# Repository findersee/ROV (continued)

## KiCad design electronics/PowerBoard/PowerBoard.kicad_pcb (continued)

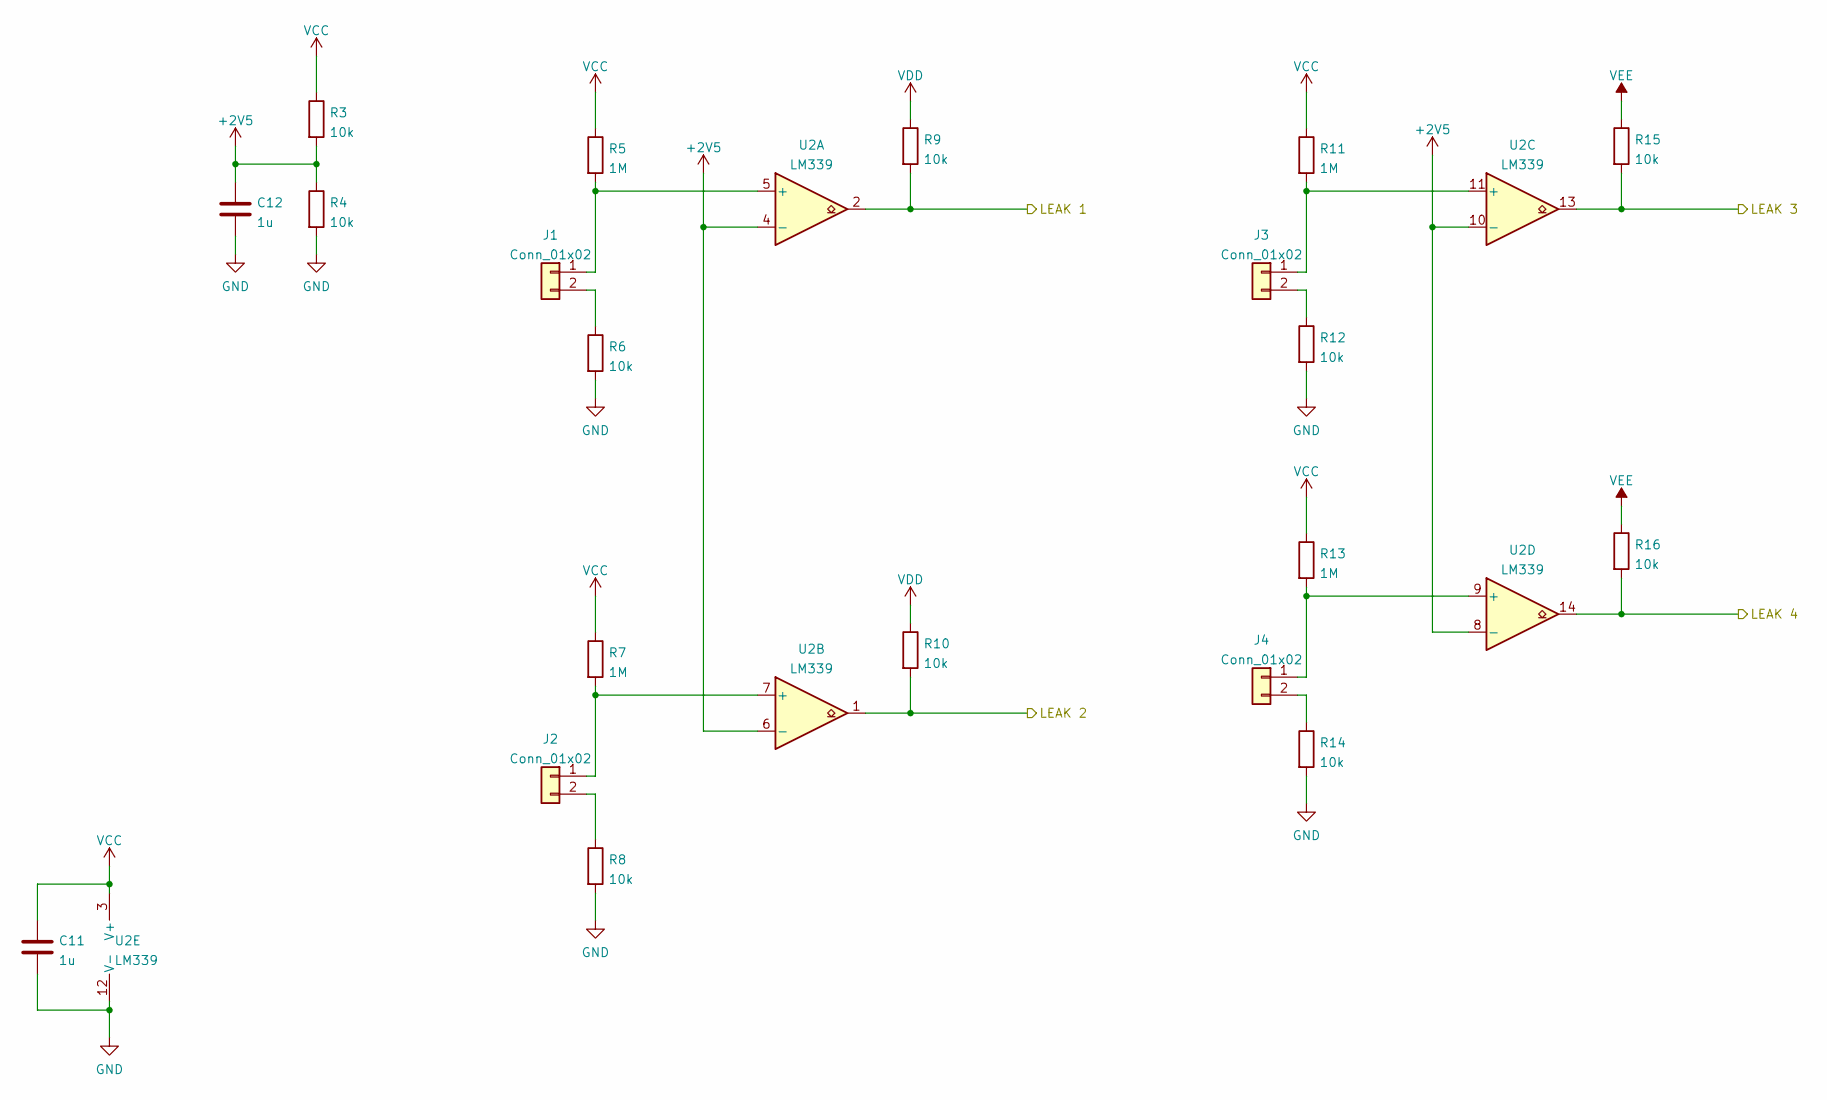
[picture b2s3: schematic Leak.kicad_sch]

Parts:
C11, C12: 1u; C_0805_2012Metric
J1, J2, J3, J4: Conn_01x02; PinHeader_1x02_P2.54mm_Vertical
R3, R4, R6, R8, R9, R10, R12, R14, R15, R16: 10k; R_0603_1608Metric
R5, R7, R11, R13: 1M; R_0603_1608Metric
U2: LM339; SOIC-14_3.9x8.7mm_P1.27mm

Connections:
+2V5: C12.1, R3.2, R4.1, U2.4 (-), U2.6 (-), U2.8 (-), U2.10 (-)
/Connectors/GP04: R10.2, U2.1; also elsewhere on the board
/Connectors/GP17: R9.2, U2.2; also elsewhere on the board
/Connectors/GP22: R15.2, U2.13; also elsewhere on the board
/Connectors/GP27: R16.2, U2.14; also elsewhere on the board
GND: C11.2, C12.2, R4.2, R6.2, R8.2, R12.2, R14.2, U2.12 (V-); also elsewhere on the board
unnamed: J1.1, R5.2, U2.5 (+)
unnamed: J1.2, R6.1
unnamed: J2.1, R7.2, U2.7 (+)
unnamed: J2.2, R8.1
unnamed: J3.1, R11.2, U2.11 (+)
unnamed: J3.2, R12.1
unnamed: J4.1, R13.2, U2.9 (+)
unnamed: J4.2, R14.1
VCC: C11.1, R3.1, R5.1, R7.1, R11.1, R13.1, U2.3 (V+); also elsewhere on the board
VDD: R9.1, R10.1; also elsewhere on the board
VEE: R15.1, R16.1; also elsewhere on the board

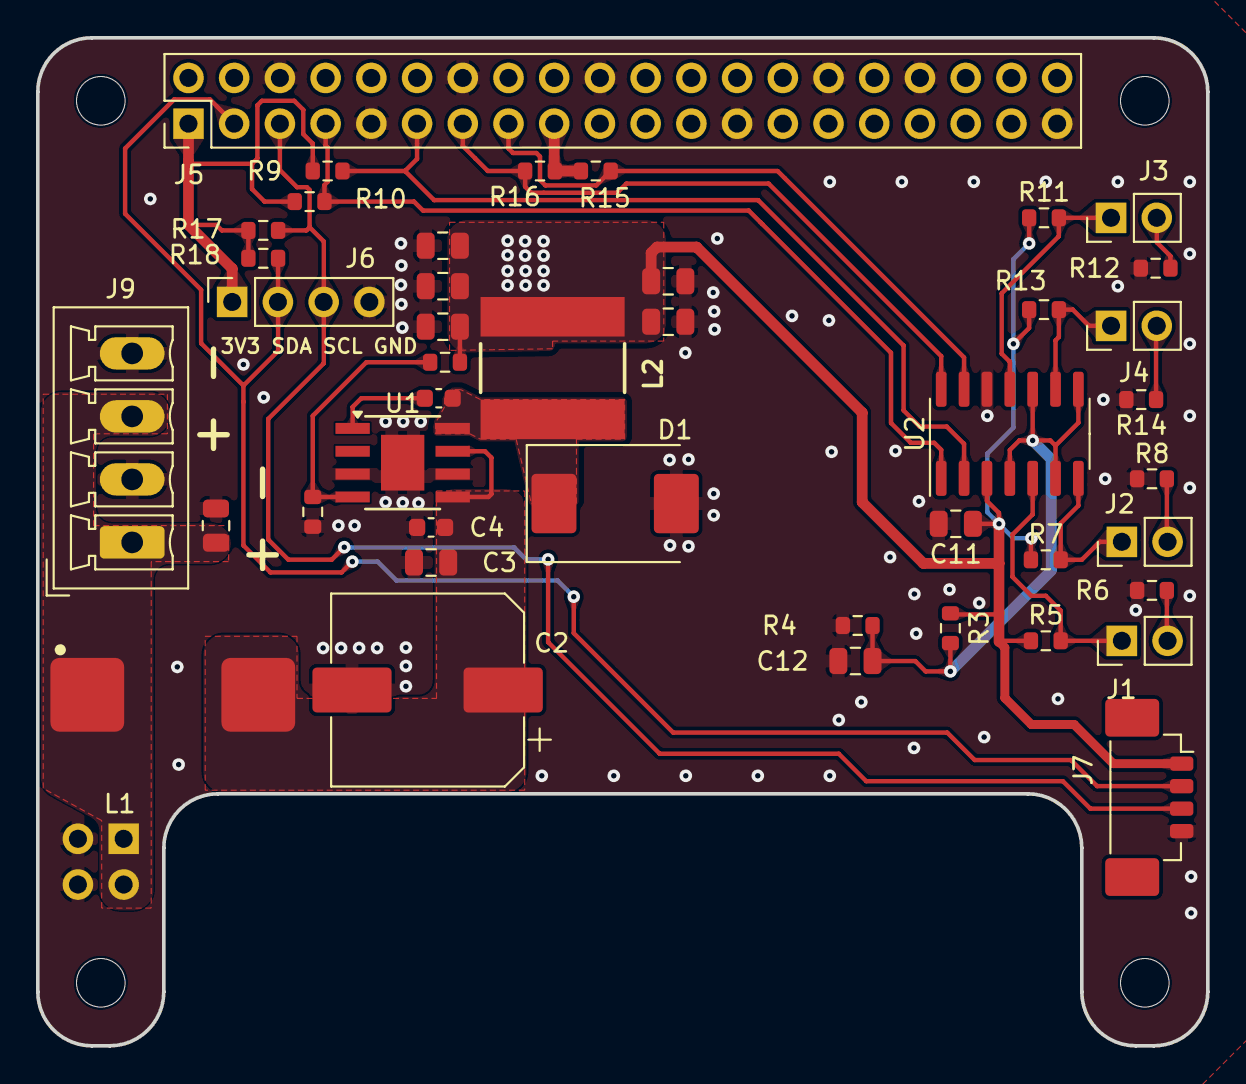
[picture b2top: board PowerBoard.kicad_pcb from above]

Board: 2 copper layers, 65.0 x 56.0 mm, 48 parts (1 on the bottom side), 24 nets.

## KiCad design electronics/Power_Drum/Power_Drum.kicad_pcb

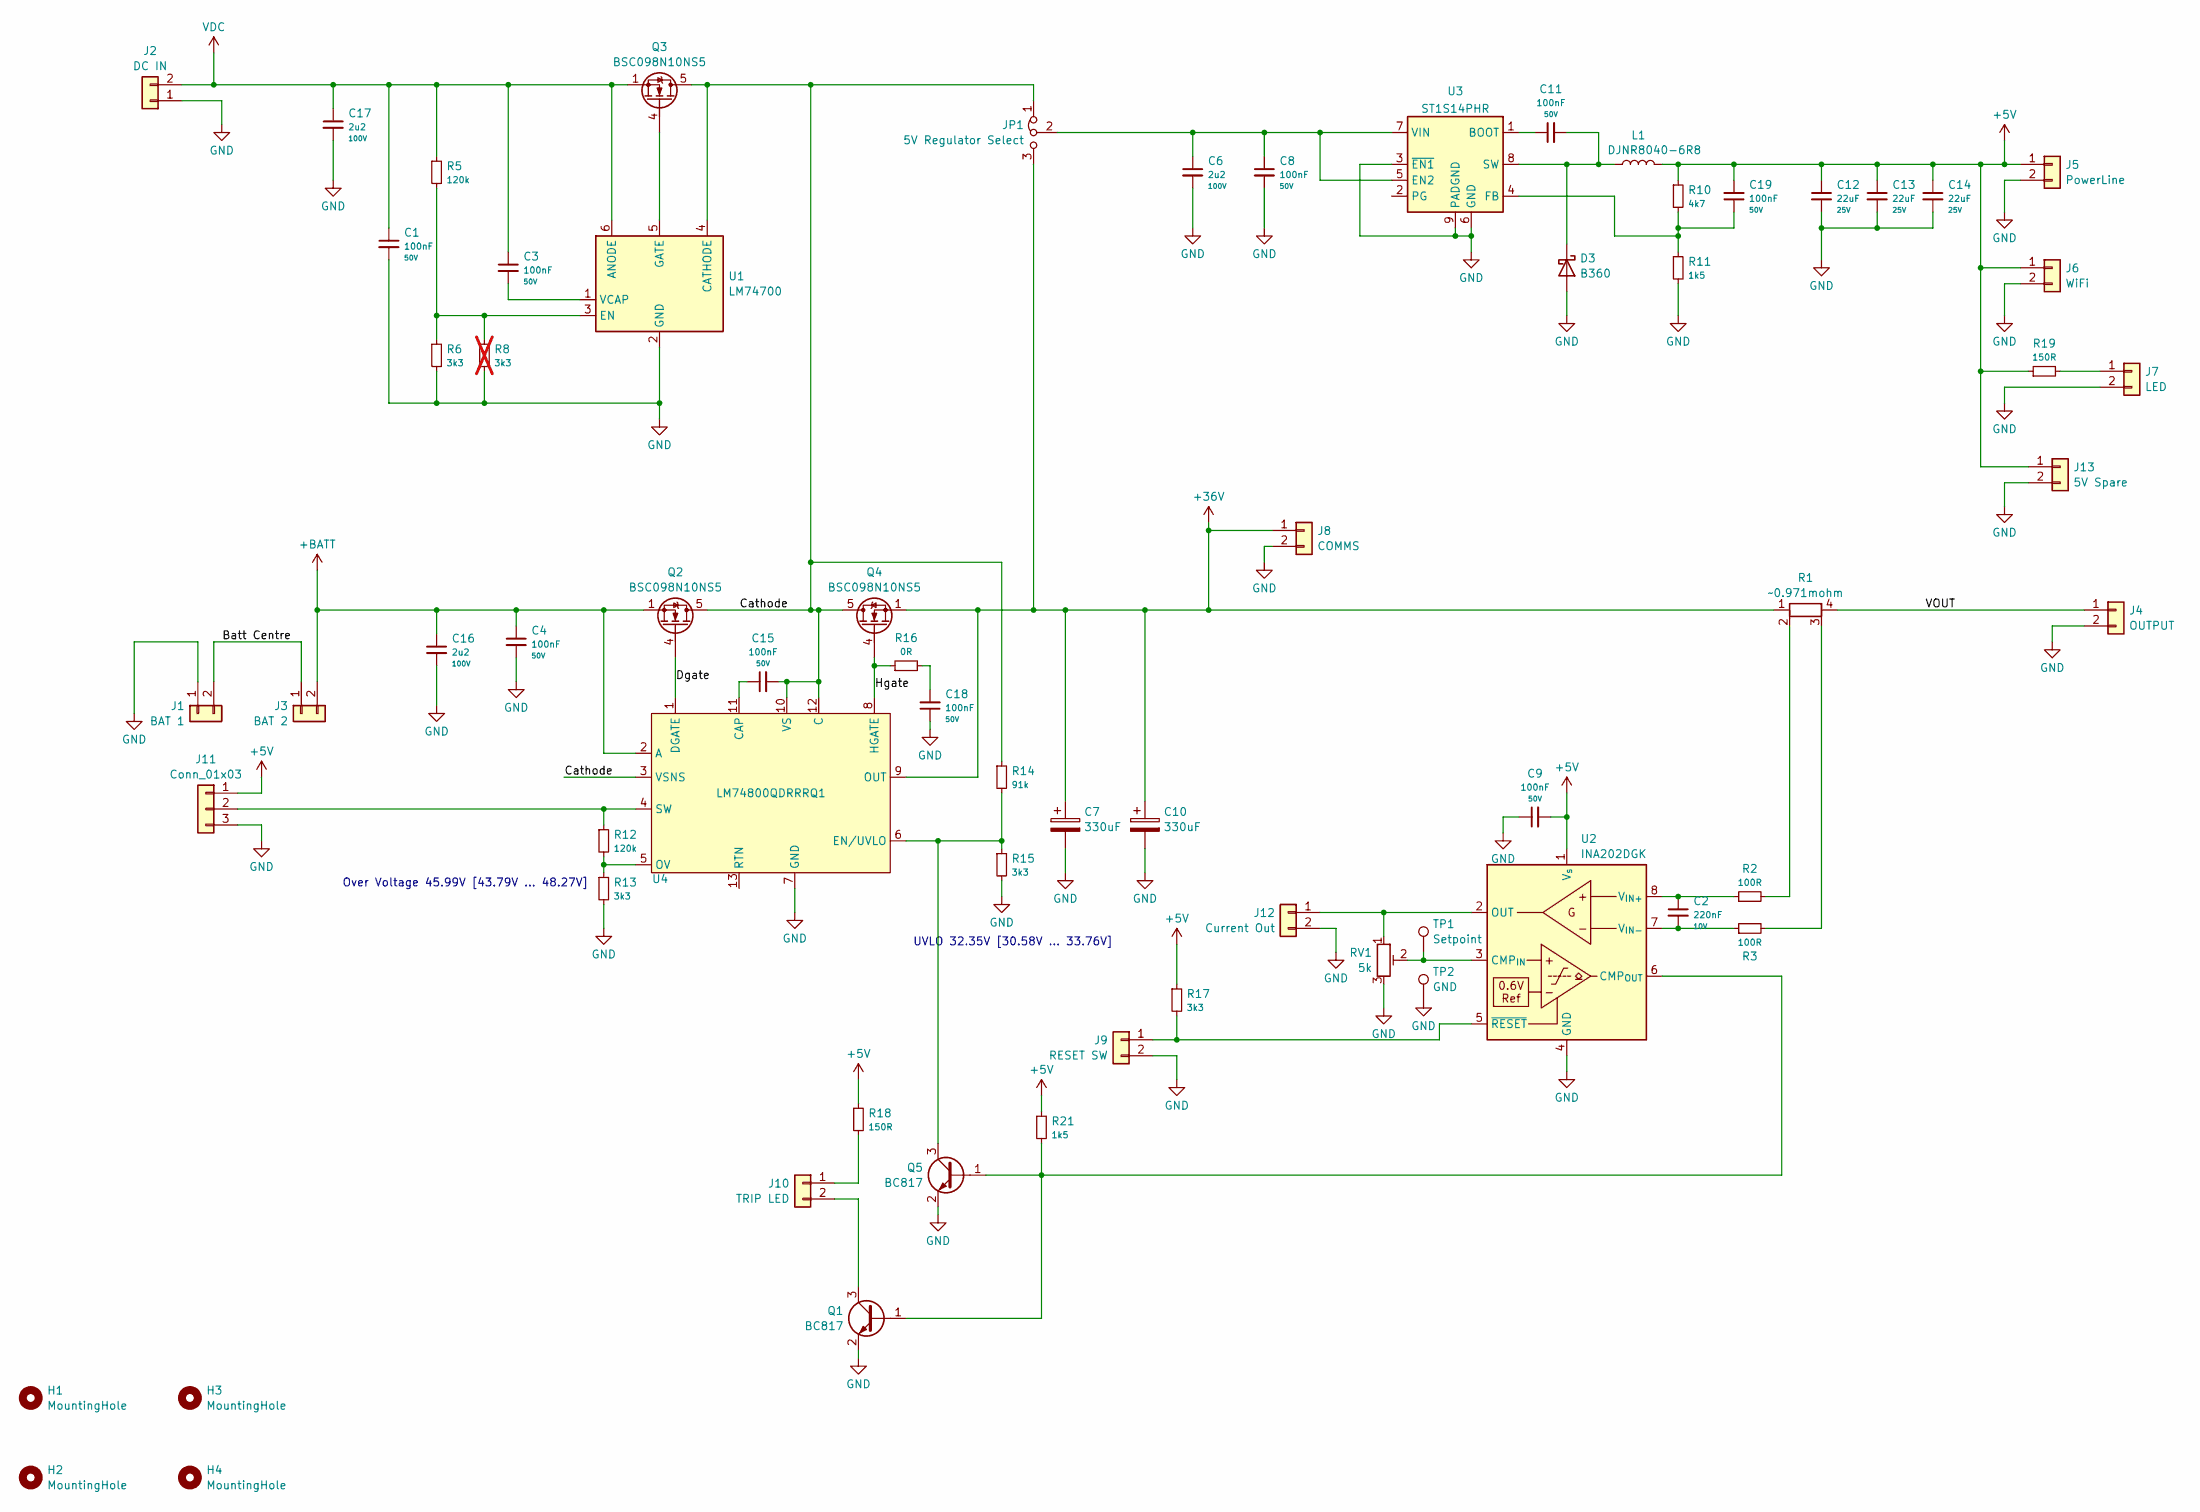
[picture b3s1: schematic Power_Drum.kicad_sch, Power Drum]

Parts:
C1, C3, C4, C8, C9, C11, C15, C18, C19: 100nF; C_0603_1608Metric; Voltage 50V
C2: 220nF; C_0402_1005Metric; Voltage 10V
C6, C16, C17: 2u2; C_0805_2012Metric; Voltage 100V
C7: 330uF; CP_Radial_D10.0mm_P5.00mm; Voltage 100V
C10: 330uF; CP_Radial_D12.5mm_P5.00mm; Voltage 100V
C12, C13, C14: 22uF; C_1210_3225Metric; Voltage 25V
D3: B360; D_SMC
H1, H2, H3, H4: MountingHole; MountingHole_3.2mm_M3_ISO14580
J1: BAT 1; TerminalBlock_Phoenix_PT-1,5-2-5.0-H_1x02_P5.00mm_Horizontal
J2: DC IN; TerminalBlock_Phoenix_PT-1,5-2-5.0-H_1x02_P5.00mm_Horizontal
J3: BAT 2; TerminalBlock_Phoenix_PT-1,5-2-5.0-H_1x02_P5.00mm_Horizontal
J4: OUTPUT; TerminalBlock_Phoenix_PT-1,5-2-5.0-H_1x02_P5.00mm_Horizontal
J5: PowerLine; TerminalBlock_Phoenix_PT-1,5-2-3.5-H_1x02_P3.50mm_Horizontal
J6: WiFi; TerminalBlock_Phoenix_PT-1,5-2-3.5-H_1x02_P3.50mm_Horizontal
J7: LED; Molex_KK-254_AE-6410-02A_1x02_P2.54mm_Vertical
J8: COMMS; PinHeader_1x02_P2.54mm_Vertical
J9: RESET SW; Molex_KK-254_AE-6410-02A_1x02_P2.54mm_Vertical
J10: TRIP LED; Molex_KK-254_AE-6410-02A_1x02_P2.54mm_Vertical
J11: Conn_01x03; PinHeader_1x03_P2.54mm_Vertical
J12: Current Out; PinHeader_1x02_P2.54mm_Vertical
J13: 5V Spare; PinHeader_1x02_P2.54mm_Vertical
JP1: 5V Regulator Select; PinHeader_1x03_P2.54mm_Vertical
L1: DJNR8040-6R8; L_Bourns_SRN8040TA
Q1, Q5: BC817; SOT-23
Q2, Q3, Q4: BSC098N10NS5; TDSON-8-1
R1: ~0.971mohm; SHUNT_5x8
R2, R3: 100R; R_0402_1005Metric
R5, R12: 120k; R_0603_1608Metric
R6, R13, R15, R17: 3k3; R_0603_1608Metric
R8: 3k3; R_0603_1608Metric; not fitted
R10: 4k7; R_0603_1608Metric
R11, R21: 1k5; R_0603_1608Metric
R14: 91k; R_0603_1608Metric
R16: 0R; R_0603_1608Metric
R18, R19: 150R; R_0603_1608Metric
RV1: 5k; Potentiometer_Bourns_3314G_Vertical
TP1: Setpoint; TestPoint_Pad_D1.0mm
TP2: GND; TestPoint_Pad_D1.0mm
U1: LM74700; SOT-23-6
U2: INA202DGK; VSSOP-8_3x3mm_P0.65mm
U3: ST1S14PHR; TI_SO-PowerPAD-8
U4: LM74800QDRRRQ1; WSON-12-1EP_3x3mm_P0.5mm_EP1.5x2.5mm

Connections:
+5V: C9.2, C12.1, C13.1, C14.1, C19.2, J5.1, J6.1, J11.1, J13.1, L1.2, R10.1, R17.1, R18.1, R19.1, R21.1, U2.1 (V_{s})
+36V: C7.1, C10.1, J8.1, JP1.3 (B), Q4.1 (S), Q4.2 (S), Q4.3 (S), R1.1, U4.9 (OUT)
+BATT: C4.1, C16.1, J3.2, Q2.1 (S), Q2.2 (S), Q2.3 (S), U4.2 (A)
/Batt Centre: J1.2, J3.1
/Cathode: C15.2, JP1.1 (A), Q2.5 (D), Q3.5 (D), Q4.5 (D), R14.1, U1.4 (CATHODE), U4.3 (VSNS), U4.10 (VS), U4.12 (C)
/Dgate: Q2.4 (G), U4.1 (DGATE)
/Hgate: Q4.4 (G), R16.1, U4.8 (HGATE)
/VOUT: J4.1, R1.4
GND: C1.2, C4.2, C6.2, C7.2, C8.2, C9.1, C10.2, C12.2, C13.2, C14.2, C16.2, C17.2, C18.1, D3.2 (A), J1.1, J2.1, J4.2, J5.2, J6.2, J7.2, J8.2, J9.2, J11.3, J12.2, J13.2, Q1.2 (E), Q5.2 (E), R6.2, R8.2, R11.2, R13.2, R15.2, RV1.3, TP2.1 (1_1), U1.2 (GND), U2.4 (GND), U3.3 (~EN1), U3.6 (GND), U3.9 (PADGND), U4.7 (GND)
unnamed: C18.2, R16.2
unnamed: C11.2, D3.1 (K), L1.1, U3.8 (SW)
unnamed: J7.1, R19.2
unnamed: J9.1, R17.2, U2.5 (~RESET)
unnamed: J10.1, R18.2
unnamed: J10.2, Q1.3 (C)
unnamed: J11.2, R12.1, U4.4 (SW)
unnamed: J12.1, RV1.1, U2.2 (OUT)
unnamed: C6.1, C8.1, JP1.2 (C), U3.5 (EN2), U3.7 (VIN)
unnamed: Q1.1 (B), Q5.1 (B), R21.2, U2.6 (CMP_{OUT})
unnamed: Q3.4 (G), U1.5 (GATE)
unnamed: Q5.3 (C), R14.2, R15.1, U4.6 (EN/UVLO)
unnamed: R1.2, R2.2
unnamed: R1.3, R3.2
unnamed: R5.2, R6.1, R8.1, U1.3 (EN)
unnamed: C3.2, U1.1 (VCAP)
unnamed: RV1.2, TP1.1 (1_1), U2.3 (CMP_{IN})
unnamed: C2.1, R2.1, U2.8 (V_{IN+})
unnamed: C2.2, R3.1, U2.7 (V_{IN-})
unnamed: C11.1, U3.1 (BOOT)
unnamed: C19.1, R10.2, R11.1, U3.4 (FB)
unnamed: C15.1, U4.11 (CAP)
unnamed: R12.2, R13.1, U4.5 (OV)
VDC: C1.1, C3.1, C17.1, J2.2, Q3.1 (S), Q3.2 (S), Q3.3 (S), R5.1, U1.6 (ANODE)

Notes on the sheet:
Over Voltage 45.99V [43.79V ... 48.27V]
UVLO 32.35V [30.58V ... 33.76V]

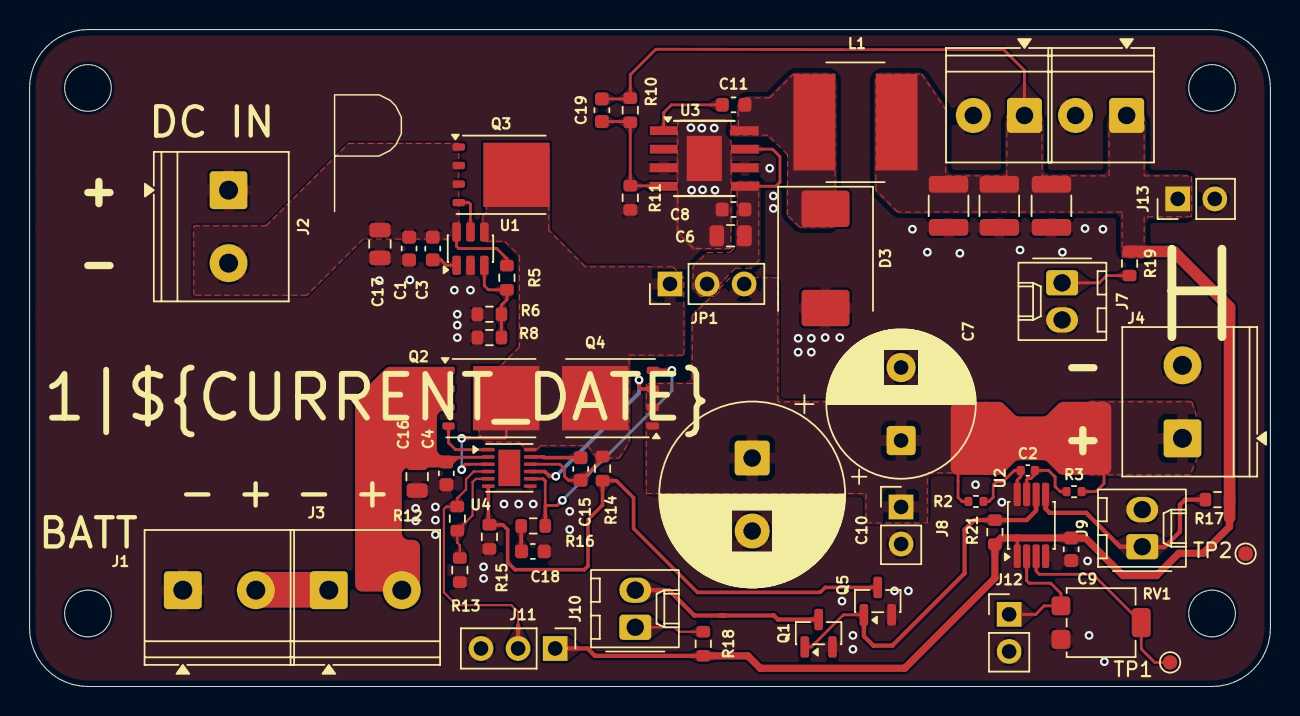
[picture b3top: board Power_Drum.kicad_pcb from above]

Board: 2 copper layers, 85.0 x 45.0 mm, 67 parts (0 on the bottom side), 33 nets.

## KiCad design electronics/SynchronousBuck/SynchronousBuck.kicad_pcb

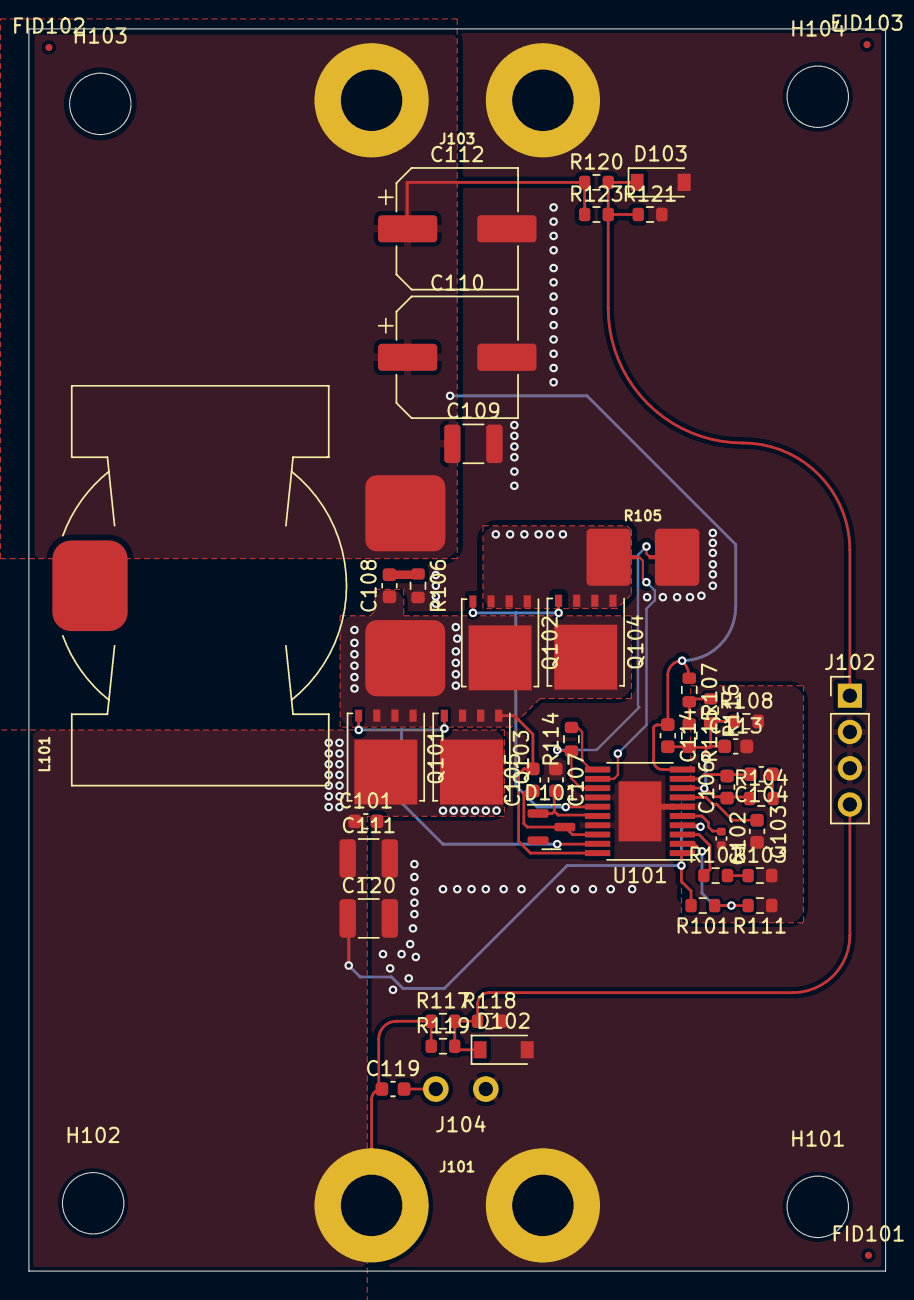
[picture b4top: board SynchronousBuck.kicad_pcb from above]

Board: 4 copper layers, 60.0 x 87.0 mm, 55 parts (0 on the bottom side), 26 nets.

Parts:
C101, C103: 100n; C_0603_1608Metric
C102: 680p; C_0402_1005Metric
C104: 560p; C_0603_1608Metric
C105, C107: 1u; C_0603_1608Metric
C106: 33p; C_0603_1608Metric
C108, C113, C114: C_Small; C_0603_1608Metric
C109, C111, C120: 2u2; C_1210_3225Metric
C110, C112: 390u; CP_Elec_8x11.9
C119: 10n; C_0603_1608Metric
D101: BAS20; SOT-23
D102, D103: 5V1; D_SOD-123
FID101, FID102, FID103: Fiducial; Fiducial_0.5mm_Mask1mm
H101, H102, H103, H104: MountingHole; MountingHole_4.3mm_M4_DIN965
J101, J103: Conn_01x02; 2xM4
J102: Conn_01x04_Male; PinHeader_1x04_P2.54mm_Vertical
J104: Conn_01x02; 1x2_3.5_pinHeader
L101: IND_7443640680_WURTH; WE-HCF
NT101: NetTie_2; NetTie-2_SMD_Pad0.5mm
Q101, Q103: BSC070N10NS5; TDSON-8-1
Q102, Q104: BSC067N06LS3G; TDSON-8-1
R101: 18k; R_0603_1608Metric
R102: 820; R_0603_1608Metric
R103: 8k2; R_0603_1608Metric
R104: 178k; R_0603_1608Metric
R105: 0R005; R_2512_6332Metric_SHUNT
R106: R_Small; R_0603_1608Metric
R107, R108, R111, R118, R121: 1k2; R_0603_1608Metric
R114: 10k; R_0603_1608Metric
R115, R116, R117, R119, R120, R123: 24k; R_0603_1608Metric
U101: LM5116MH; Texas_PWP0020A

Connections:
/FB: C106.1, C113.1, C114.2, R104.1, R108.1, R115.2, R116.2, U101.8 (FB)
/HO: Q101.4 (G), Q103.4 (G), U101.19 (HO)
/LO: Q102.4 (G), Q104.4 (G), U101.15 (LO)
/SW: C105.2, C108.1, L101.1, Q101.1 (S), Q101.2 (S), Q101.3 (S), Q102.5 (D), Q103.1 (S), Q103.2 (S), Q103.3 (S), Q104.5 (D), U101.20 (SW)
/ShuntTop: Q102.1 (S), Q102.2 (S), Q102.3 (S), Q104.1 (S), Q104.2 (S), Q104.3 (S), R105.1
/VOUT: C109.1, C110.1, C112.1, C114.1, J103.1, L101.2, R107.1, R120.1, R123.1, U101.10 (VOUT)
GND: C101.2, C107.1, C109.2, C110.2, C111.2, C112.2, C120.2, D102.2 (A), D103.2 (A), J101.1, J102.2, J102.3, J103.2, J104.2, NT101.2, R105.4, R106.2, R118.2, R121.2, U101.14 (PGND), U101.17 (VCCX), U101.21 (EP)
GNDA: C102.2, C103.2, C113.2, NT101.1, R103.2, R108.2, R111.1, U101.6 (AGND)
unnamed: C102.1, U101.5 (RAMP)
unnamed: C103.1, U101.7 (SS)
unnamed: C104.1, R104.2
unnamed: C104.2, C106.2, U101.9 (COMP)
unnamed: C105.1, D101.3 (K), U101.18 (HB)
unnamed: C107.2, D101.1 (A), U101.16 (VCC)
unnamed: C108.2, R106.1
unnamed: C119.2, J104.1
unnamed: D102.1 (K), J102.4, R117.2, R118.1, R119.2
unnamed: D103.1 (K), J102.1, R120.2, R121.1, R123.2
unnamed: R101.1, R111.2, U101.2 (UVLO)
unnamed: R102.1, U101.3 (RT/SYNC)
unnamed: R102.2, R103.1
unnamed: R105.2, U101.12 (CS)
unnamed: R105.3, R114.1, U101.13 (CSG)
unnamed: R107.2, R115.1, R116.1
unnamed: R114.2, U101.11 (DEMB)
VCC: C101.1, C111.1, C119.1, C120.1, J101.2, Q101.5 (D), Q103.5 (D), R101.2, R117.1, R119.1, U101.1 (VIN), U101.4 (EN)

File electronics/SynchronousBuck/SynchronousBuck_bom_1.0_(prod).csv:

Component,Description,Part,References,Value,Footprint,Quantity Per PCB,Datasheet,LCSC Pn,Voltage,Config,Manufacturer Pn,Manufacturer,Status,Manufacturer #,Family,Component Value,Part#,LSCS Part#
1,"Unpolarized capacitor, small symbol",C_Small,C101 C103,100n,C_0603_1608Metric,2,~,C386106,50V,,,,,,,,,
2,"Unpolarized capacitor, small symbol",C_Small,C119,10n,C_0603_1608Metric,1,~,C57112,,,,,,,,,,
3,"Unpolarized capacitor, small symbol",C_Small,C105 C107,1u,C_0603_1608Metric,2,~,,,,,,,,,,,
4,"Unpolarized capacitor, small symbol",C_Small,C109 C111 C120,2u2,C_1210_3225Metric,3,~,C153036,100 V,,,,,,,,,
5,"Unpolarized capacitor, small symbol",C_Small,C102,680p,C_0402_1005Metric,1,~,C307451,,,,,,,,,,
6,Zener diode,D_Zener,D102 D103,5V1,D_SOD-123,2,~,C173407,,,,,,,,,,
7,"200V, 0.4A, High-speed Switching Diode, SOT-23",BAS20,D101,BAS20,SOT-23,1,https://www.diodes.com/assets/Datasheets/Ds12004.pdf,,,,,,,,,,,
8,"25A Id, 30V Vds, NexFET N-Channel Power MOSFET, 6.9mOhm Ron, Qg (typ) 7.9nC, SON8 5x6mm",BSC067N06LS3G,Q102,BSC067N06LS3G,TDSON-8-1,1,https://www.infineon.com/dgdl/Infineon-BSC067N06LS3-DS-v02_0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,C24199,,,,,,,,,,
9,"80A Id, 100V Vds, OptiMOS N-Channel Power MOSFET, 7.0mOhm Ron, Qg (typ) 30.0nC, PG-TDSON-8",BSC070N10NS5,Q101,BSC070N10NS5,TDSON-8-1,1,http://www.infineon.com/dgdl/Infineon-BSC070N10NS5-DS-v02_01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,C151549,,,,,,,,,,
10,Shunt resistor,R_Shunt,R105,0R005,LR2512_3WLOW_SHUNT,1,~,C154688,,,,,,,,,,
11,"Resistor, small symbol",R_Small,R112 R113,100,R_0603_1608Metric,2,~,,,,,,,,,,,
12,"Resistor, small symbol",R_Small,R114,10k,R_0603_1608Metric,1,~,,,,,,,,,,,
13,"Resistor, small symbol",R_Small,R101,18k,R_0603_1608Metric,1,~,,,,,,,,,,,
14,"Resistor, small symbol",R_Small,R107 R108 R111 R118 R121,1k2,R_0603_1608Metric,5,~,,,,,,,,,,,
15,"Resistor, small symbol",R_Small,R115 R116 R117 R119 R120 R123,24k,R_0603_1608Metric,6,~,,,,,,,,,,,
16,"Resistor, small symbol",R_Small,R102,820,R_0603_1608Metric,1,~,,,,,,,,,,,
17,"Resistor, small symbol",R_Small,R103,8k2,R_0603_1608Metric,1,~,,,,,,,,,,,
18,"Wide Voltage Range Buck Controller, HTSSOP-20",LM5116MH,U101,LM5116MH,Texas_PWP0020A,1,https://www.ti.com/lit/ds/symlink/lm5116.pdf,,,,,Texas Instruments,,,,,LM5116MH/NOPB,C13755





Component Groups:,28
Component Count:,47
Fitted Components:,33
Number of PCBs:,1
Total components:,33
Schematic Version:,1.0
Schematic Date:,2021-06-07
PCB Variant:,prod
BoM Date:,10/06/2021 19:02:05
Schematic Source:,C:\Users\akiku\GIT\ROV\electronics\SynchronousBuck\SynchronousBuck.sch
KiCad Version:,Eeschema (5.1.7)-1

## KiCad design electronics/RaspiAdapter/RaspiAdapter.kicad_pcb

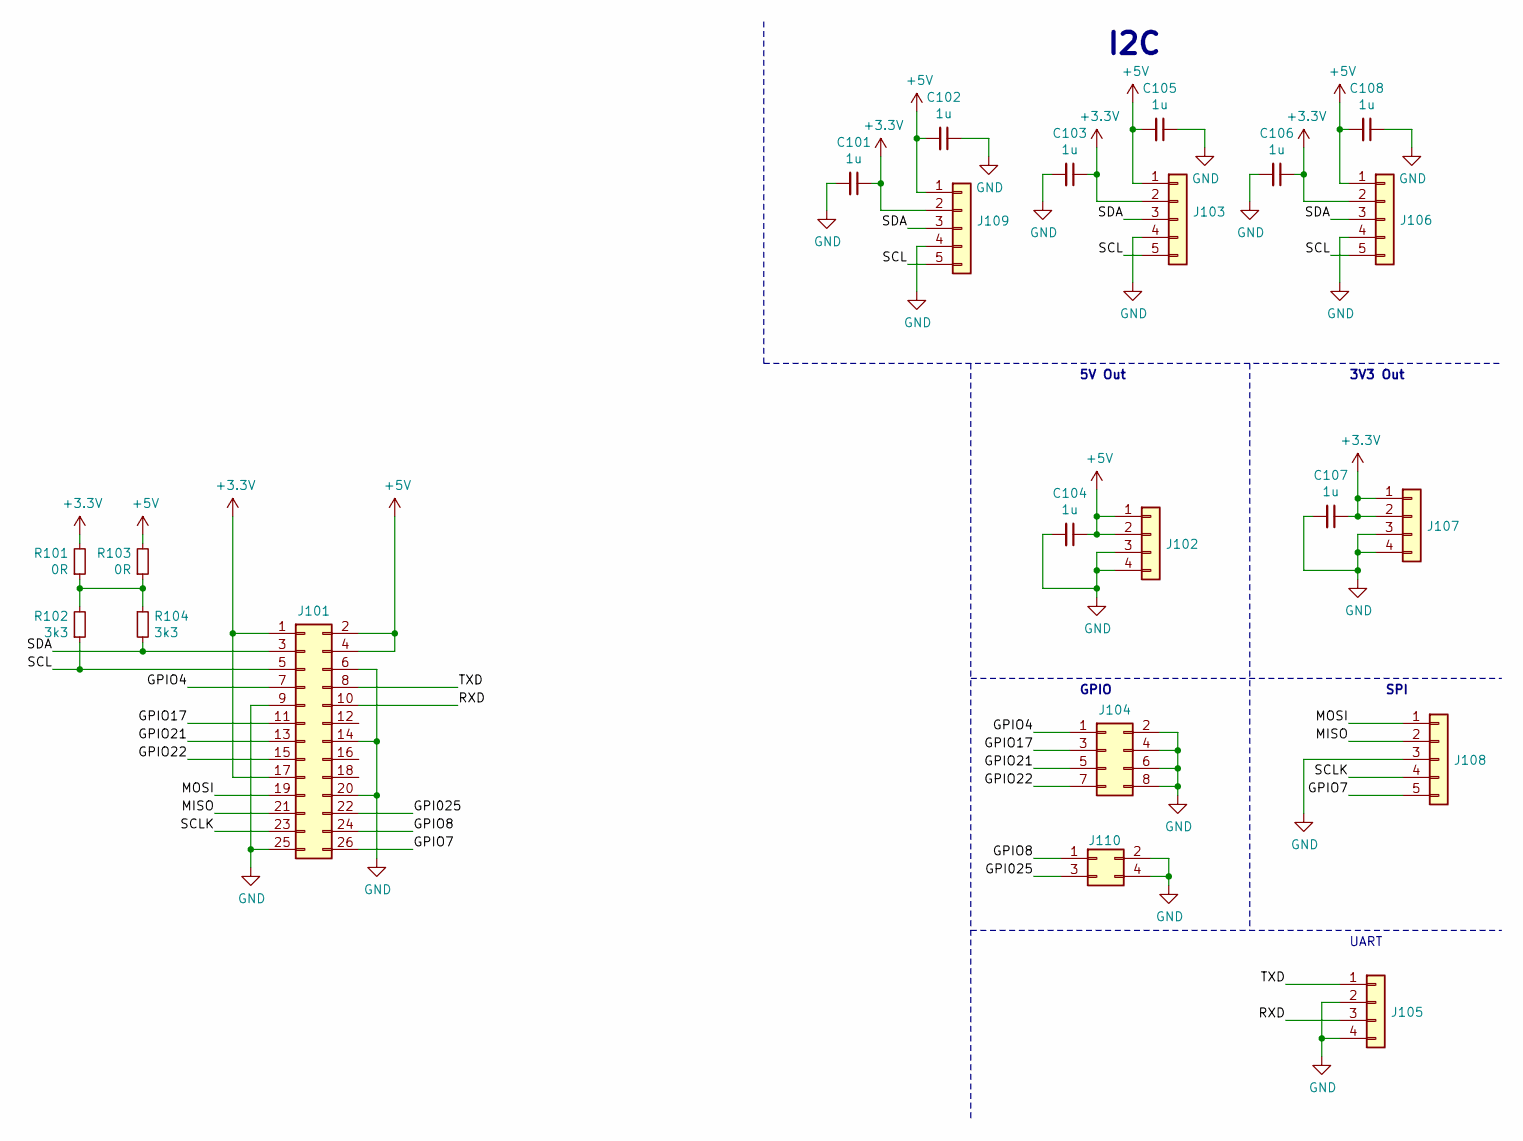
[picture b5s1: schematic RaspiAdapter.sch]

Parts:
C101, C102, C103, C104, C105, C106, C107, C108: 1u; C_0603_1608Metric_Pad1.05x0.95mm_HandSolder
J101: Conn_02x13_Odd_Even; PinHeader_2x13_P2.54mm_Vertical
J102: Conn_01x04; PinHeader_2x02_P2.54mm_Vertical
J103, J106, J108, J109: Conn_01x05; PinHeader_1x05_P2.54mm_Vertical
J104: Conn_02x04_Odd_Even; PinSocket_2x04_P2.54mm_Vertical
J105, J107, J110: Conn_01x04; PinSocket_2x02_P2.54mm_Vertical
R101, R103: 0R; R_0603_1608Metric_Pad0.98x0.95mm_HandSolder
R102, R104: 3k3; R_0603_1608Metric_Pad0.98x0.95mm_HandSolder

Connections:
+3V3: C101.1, C103.1, C106.1, C107.1, J101.1, J101.17, J103.2, J106.2, J107.1, J107.2, J109.2, R101.2
+5V: C102.2, C104.1, C105.2, C108.2, J101.2, J101.4, J102.1, J102.2, J103.1, J106.1, J109.1, R103.2
/GPI025: J101.22, J110.3
/GPIO4: J101.7, J104.1
/GPIO7: J101.26, J108.5
/GPIO8: J101.24, J110.1
/GPIO17: J101.11, J104.3
/GPIO21: J101.13, J104.5
/GPIO22: J101.15, J104.7
/MISO: J101.21, J108.2
/MOSI: J101.19, J108.1
/RXD: J101.10, J105.3
/SCL: J101.5, J103.5, J106.5, J109.5, R102.1
/SCLK: J101.23, J108.4
/SDA: J101.3, J103.3, J106.3, J109.3, R104.2
/TXD: J101.8, J105.1
GND: C101.2, C102.1, C103.2, C104.2, C105.1, C106.2, C107.2, C108.1, J101.6, J101.9, J101.14, J101.20, J101.25, J102.3, J102.4, J103.4, J104.2, J104.4, J104.6, J104.8, J105.2, J105.4, J106.4, J107.3, J107.4, J108.3, J109.4, J110.2, J110.4
unnamed: R101.1, R102.2, R103.1, R104.1

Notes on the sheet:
UART
SPI
GPIO
3V3 Out
5V Out
I2C

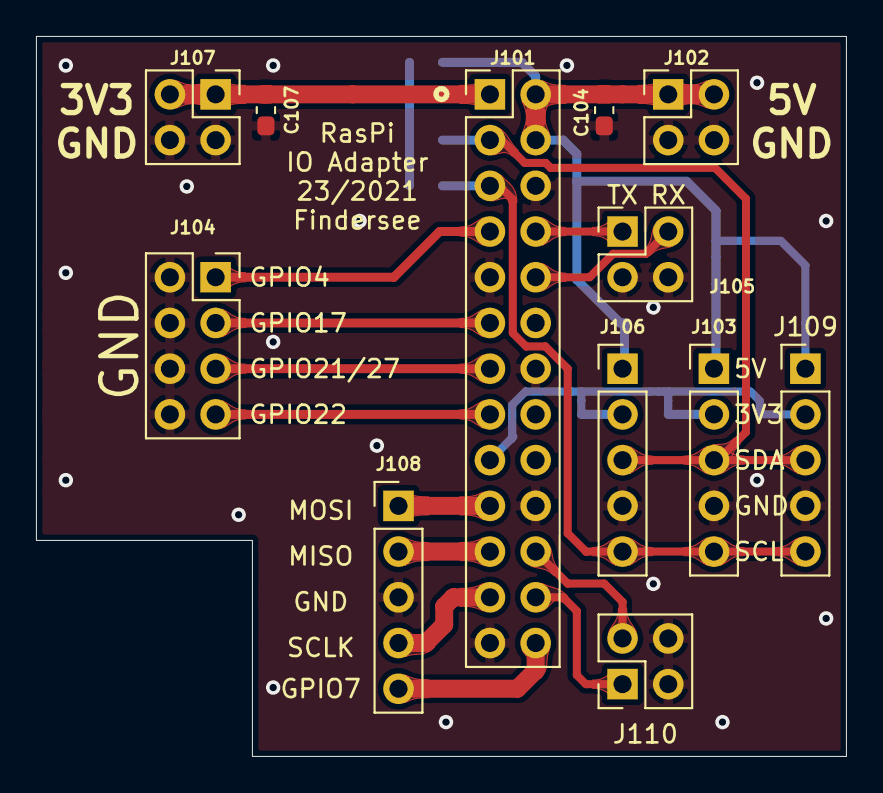
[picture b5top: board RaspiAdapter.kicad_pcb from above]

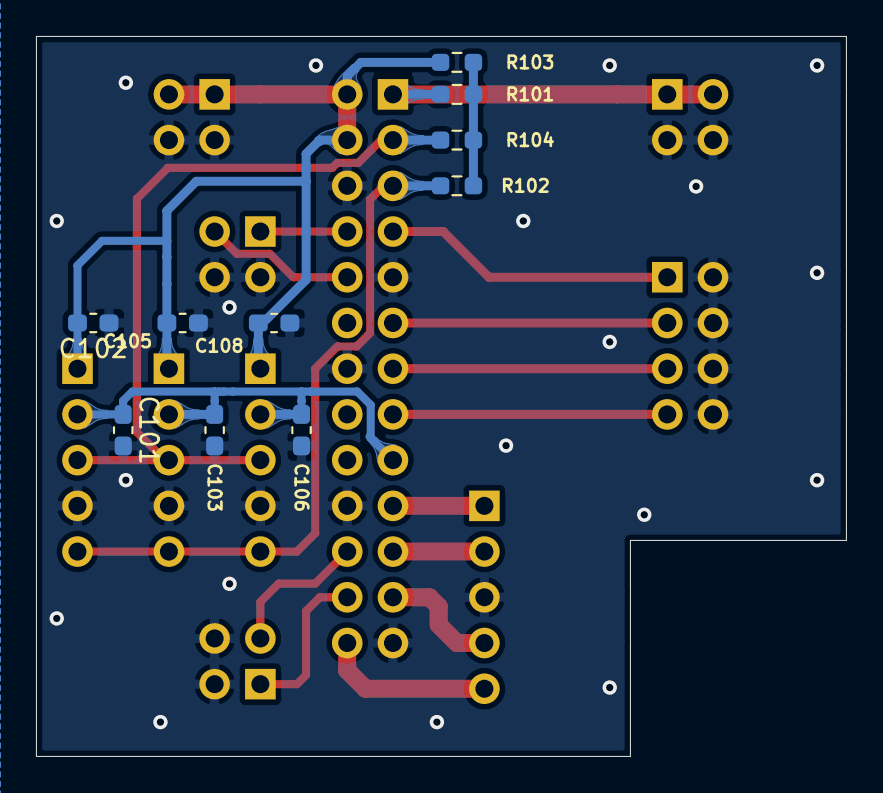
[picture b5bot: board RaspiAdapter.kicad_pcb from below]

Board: 2 copper layers, 45.0 x 40.0 mm, 22 parts (10 on the bottom side), 18 nets.

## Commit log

2021-04-22 GUI Commit
2021-06-07 Added electronics Parts
2021-06-07 Updated layout and schematic. Added zener diodes to protect output of measurements
2021-06-08 Cleaning silks and moving components
2021-06-08 More silkscreen fixing
2021-06-08 Even more silkscreen fixes
2021-06-08 BOM optimization for JLCPcb assembly
2021-06-09 Added Raspi Adapter Changed Buck Capacitors
2021-06-09 New Fabrication files
2021-06-09 Updated BOM
2021-06-09 Cramp value fix Updated schematic PDF
2021-06-10 Production Commit
2021-06-13 Updated software
2021-06-13 Removed old software
2022-01-25 Updated SW
2022-01-30 update gitignore
2022-02-02 Removed ssl key
2023-01-03 Hat Addition
2023-01-13 Changed To RPI Pico Module
2023-01-14 Layout Done first level
2023-01-14 Fabrication commit
2023-01-14 Fabrication commit 2
2023-01-26 Final Version
2023-02-05 Folder restructuring
2023-02-05 Restructuring
2023-02-05 Added RovHat Code
2023-02-10 Added pico-ads1115
2023-02-10 Added FreeRTOS-Kernel
2023-02-10 Added Freertos Kernel
2023-02-14 Removed ads1115 submodule Started new driver
2023-02-14 Driver update
2023-02-15 Driver updates
2023-02-16 Added PWM output init Added PIN Init
2023-02-17 Dshot PIO code added
2023-02-17 Added ESC pin definitions
2023-02-18 Dshot.pio Timing correction
2023-02-19 Made ADC task and FreeRTOS setup functions
2023-02-20 Added Dshot library and freeRTOS scheduler startup
2023-02-22 Started UART_Handler_task
2023-02-25 Autodepth task started
2023-04-08 User modification
2023-04-12 Moved main.h to root
2023-04-14 Uart testing Update
2023-05-03 DShot commenting
2023-05-04 Added repeating timer for DShot
2023-05-06 Serial protocol improvements
2023-05-07 Improved ADC Task functions -Added rolling average -Removed ADC queue
2023-06-23 Fixed Analog read task
2023-07-02 Hat control code added
2023-07-08 Added PowerBoard pcb data
2023-07-25 ROV python and hat integration commit Python side
2023-07-26 Integration version of RovHat code
2023-07-26 PowerBoard commit
2023-08-07 Dry test fixes commit
2026-06-21 Multiple fixes
2026-06-22 Addded power drum electronics V1
2026-06-22 Power Drum V2 update
2026-06-29 Manufacturing commit
